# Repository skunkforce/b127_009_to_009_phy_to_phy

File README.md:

# edgy_board number b127
Use this if you want to connect two phys together without cable, magnetics or connectors. 
[view in borwser with kiCnvas](https://kicanvas.org/?github=https://github.com/skunkforce/b127_009_to_009_phy_to_phy/tree/master/board)

This design is part of the [edgy board project](https://github.com/skunkforce/edgy_boards).

# getting started
This repository uses submodules. After cloning use the command 

```$ git submodule update --init --recursive```

to pull the submodules before opening the project with kicad. 

# Tests
Tests can be found in [TESTS.md](TESTS.md)

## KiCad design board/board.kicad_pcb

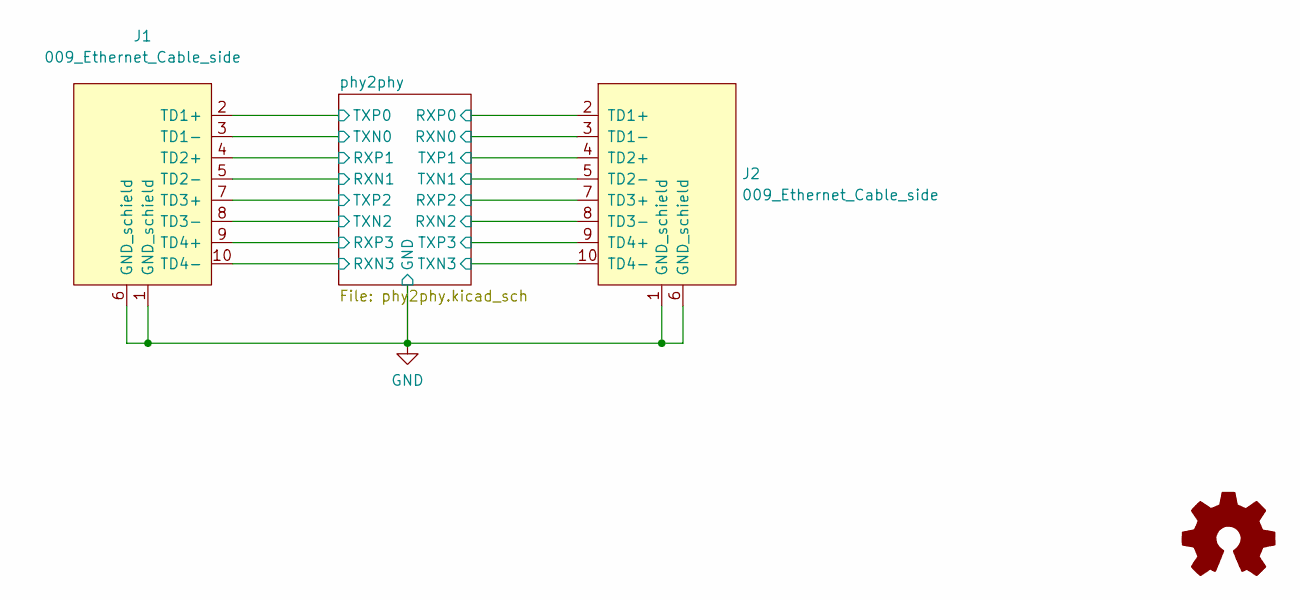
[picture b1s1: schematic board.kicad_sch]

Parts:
J1, J2: 009_Ethernet_Cable_side; on_edge_2x05_device
LOGO1: Logo_Open_Hardware_Small; OSHW-Symbol_6.7x6mm_SilkScreen

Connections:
/phy2phy/RXN0: J2.3 (TD1-); also elsewhere on the board
/phy2phy/RXN1: J1.5 (TD2-); also elsewhere on the board
/phy2phy/RXN2: J2.8 (TD3-); also elsewhere on the board
/phy2phy/RXN3: J1.10 (TD4-); also elsewhere on the board
/phy2phy/RXP0: J2.2 (TD1+); also elsewhere on the board
/phy2phy/RXP1: J1.4 (TD2+); also elsewhere on the board
/phy2phy/RXP2: J2.7 (TD3+); also elsewhere on the board
/phy2phy/RXP3: J1.9 (TD4+); also elsewhere on the board
/phy2phy/TXN0: J1.3 (TD1-); also elsewhere on the board
/phy2phy/TXN1: J2.5 (TD2-); also elsewhere on the board
/phy2phy/TXN2: J1.8 (TD3-); also elsewhere on the board
/phy2phy/TXN3: J2.10 (TD4-); also elsewhere on the board
/phy2phy/TXP0: J1.2 (TD1+); also elsewhere on the board
/phy2phy/TXP1: J2.4 (TD2+); also elsewhere on the board
/phy2phy/TXP2: J1.7 (TD3+); also elsewhere on the board
/phy2phy/TXP3: J2.9 (TD4+); also elsewhere on the board
GND: J1.1 (GND_schield), J1.6 (GND_schield), J2.1 (GND_schield), J2.6 (GND_schield); also elsewhere on the board

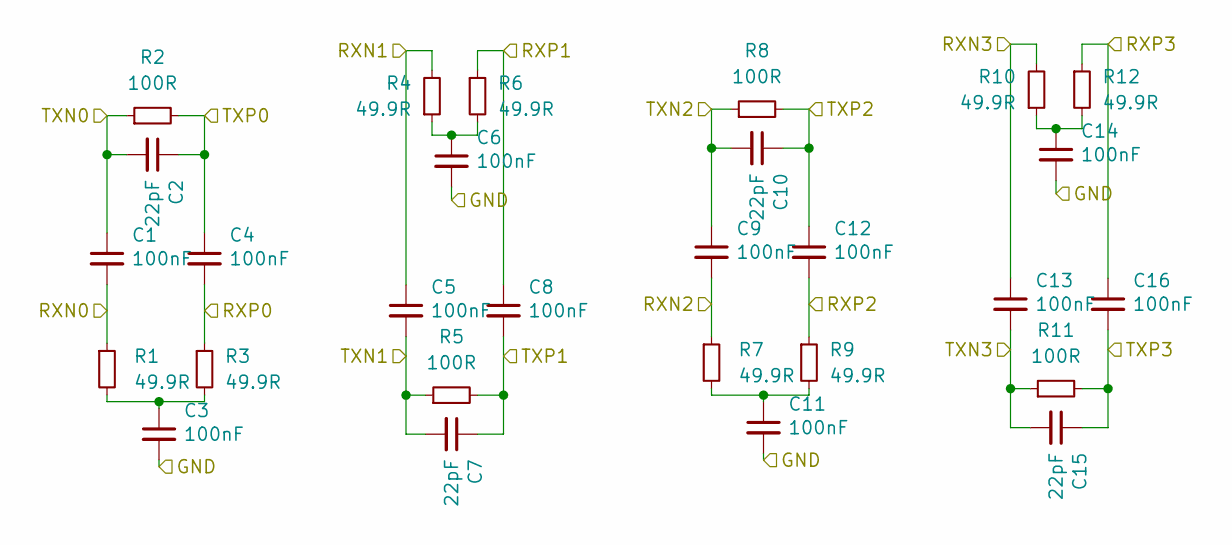
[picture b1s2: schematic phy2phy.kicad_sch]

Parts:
C1, C3, C4, C5, C6, C8, C9, C11, C12, C13, C14, C16: 100nF; C_0402_1005Metric; lcsc C307331
C2, C7, C10, C15: 22pF; C_0402_1005Metric; lcsc C1555
R1, R3, R4, R6, R7, R9, R10, R12: 49.9R; R_0402_1005Metric; lcsc C25120
R2, R5, R8, R11: 100R; R_0402_1005Metric; lcsc C25076

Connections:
/phy2phy/RXN0: C1.2, R1.1; also elsewhere on the board
/phy2phy/RXN1: C5.1, R4.2; also elsewhere on the board
/phy2phy/RXN2: C9.2, R7.1; also elsewhere on the board
/phy2phy/RXN3: C13.1, R10.2; also elsewhere on the board
/phy2phy/RXP0: C4.2, R3.1; also elsewhere on the board
/phy2phy/RXP1: C8.1, R6.1; also elsewhere on the board
/phy2phy/RXP2: C12.2, R9.1; also elsewhere on the board
/phy2phy/RXP3: C16.1, R12.1; also elsewhere on the board
/phy2phy/TXN0: C1.1, C2.2, R2.1; also elsewhere on the board
/phy2phy/TXN1: C5.2, C7.2, R5.1; also elsewhere on the board
/phy2phy/TXN2: C9.1, C10.2, R8.1; also elsewhere on the board
/phy2phy/TXN3: C13.2, C15.2, R11.1; also elsewhere on the board
/phy2phy/TXP0: C2.1, C4.1, R2.2; also elsewhere on the board
/phy2phy/TXP1: C7.1, C8.2, R5.2; also elsewhere on the board
/phy2phy/TXP2: C10.1, C12.1, R8.2; also elsewhere on the board
/phy2phy/TXP3: C15.1, C16.2, R11.2; also elsewhere on the board
GND: C3.2, C6.2, C11.2, C14.2; also elsewhere on the board
unnamed: C3.1, R1.2, R3.2
unnamed: C6.1, R4.1, R6.2
unnamed: C11.1, R7.2, R9.2
unnamed: C14.1, R10.1, R12.2

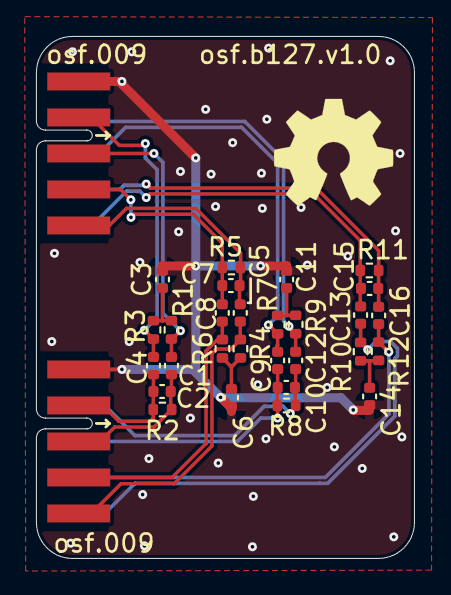
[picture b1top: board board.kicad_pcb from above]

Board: 2 copper layers, 21.0 x 29.0 mm, 31 parts (0 on the bottom side), 21 nets.

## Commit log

2023-04-22 initial
2024-01-30 fixed kiCanvas link in README.md
2024-01-30 added JLC production data
